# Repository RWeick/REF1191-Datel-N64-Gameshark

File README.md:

# REF1191-Datel-N64-Gameshark
The Kicad files for the REF1191 N64 Gameshark PCB

The edge connector spacing has been corrected from Datel's 2.54 mm to the N64 spec of 2.5 mm.

PCB Thickness: 1.2 mm

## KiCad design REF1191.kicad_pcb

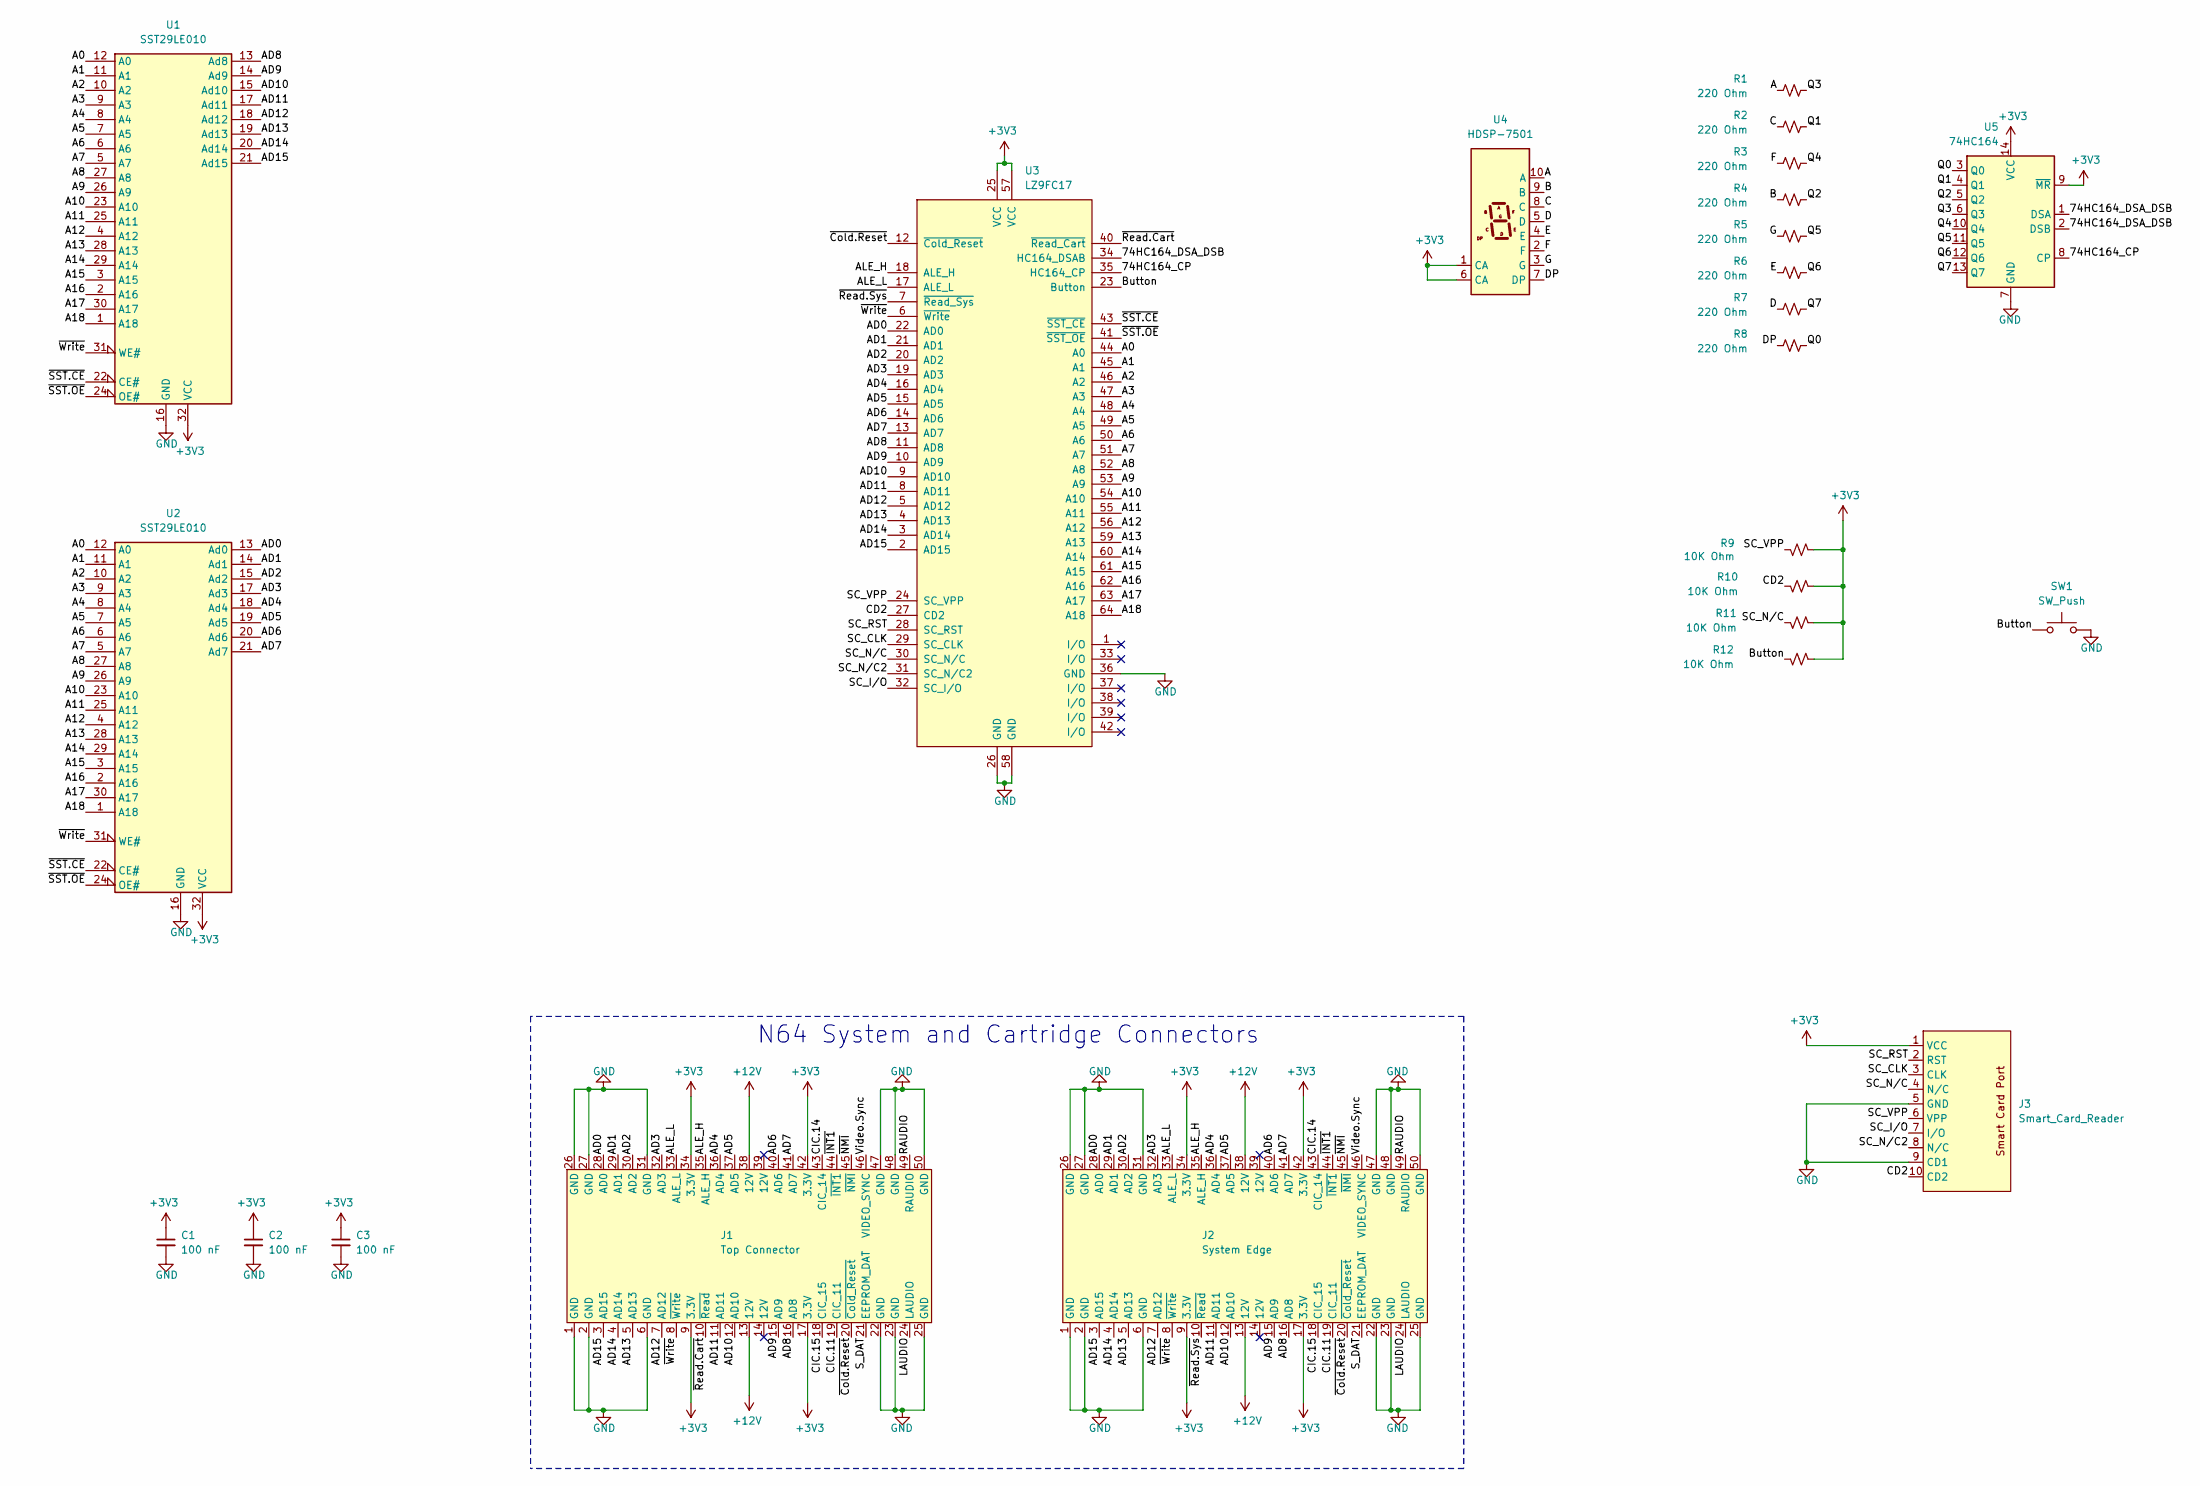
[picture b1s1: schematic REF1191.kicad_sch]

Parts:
C1, C2, C3: 100 nF; 1206 Cap Res
J1: Top Connector; Edge Connector
J2: System Edge; Edge Connector
J3: Smart_Card_Reader; Smart Card Port
R1, R2, R3, R4, R5, R6, R7, R8: 220 Ohm; 0805 Res
R9, R10, R11, R12: 10K Ohm; 1206 Cap Res
SW1: SW_Push; Button
U1, U2: SST29LE010; EEPROM
U3: LZ9FC17
U4: HDSP-7501
U5: 74HC164

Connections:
+3V3: C1.1, C2.1, C3.1, J1.9 (3.3V), J1.17 (3.3V), J1.34 (3.3V), J1.42 (3.3V), J2.9 (3.3V), J2.17 (3.3V), J2.34 (3.3V), J2.42 (3.3V), J3.1 (VCC), R9.2, R10.2, R11.2, R12.2, U1.32 (VCC), U2.32 (VCC), U3.25 (VCC), U3.57 (VCC), U4.1 (CA), U4.6 (CA), U5.9 (~MR), U5.14 (VCC)
+12V: J1.13 (12V), J1.38 (12V), J2.13 (12V), J2.38 (12V)
/74HC164_CP: U3.35 (HC164_CP), U5.8 (CP)
/74HC164_DSA_DSB: U3.34 (HC164_DSAB), U5.1 (DSA), U5.2 (DSB)
/A: R1.1, U4.10 (A)
/A0: U1.12 (A0), U2.12 (A0), U3.44 (A0)
/A1: U1.11 (A1), U2.11 (A1), U3.45 (A1)
/A2: U1.10 (A2), U2.10 (A2), U3.46 (A2)
/A3: U1.9 (A3), U2.9 (A3), U3.47 (A3)
/A4: U1.8 (A4), U2.8 (A4), U3.48 (A4)
/A5: U1.7 (A5), U2.7 (A5), U3.49 (A5)
/A6: U1.6 (A6), U2.6 (A6), U3.50 (A6)
/A7: U1.5 (A7), U2.5 (A7), U3.51 (A7)
/A8: U1.27 (A8), U2.27 (A8), U3.52 (A8)
/A9: U1.26 (A9), U2.26 (A9), U3.53 (A9)
/A10: U1.23 (A10), U2.23 (A10), U3.54 (A10)
/A11: U1.25 (A11), U2.25 (A11), U3.55 (A11)
/A12: U1.4 (A12), U2.4 (A12), U3.56 (A12)
/A13: U1.28 (A13), U2.28 (A13), U3.59 (A13)
/A14: U1.29 (A14), U2.29 (A14), U3.60 (A14)
/A15: U1.3 (A15), U2.3 (A15), U3.61 (A15)
/A16: U1.2 (A16), U2.2 (A16), U3.62 (A16)
/A17: U1.30 (A17), U2.30 (A17), U3.63 (A17)
/A18: U1.1 (A18), U2.1 (A18), U3.64 (A18)
/AD0: J1.28 (AD0), J2.28 (AD0), U2.13 (Ad0), U3.22 (AD0)
/AD1: J1.29 (AD1), J2.29 (AD1), U2.14 (Ad1), U3.21 (AD1)
/AD2: J1.30 (AD2), J2.30 (AD2), U2.15 (Ad2), U3.20 (AD2)
/AD3: J1.32 (AD3), J2.32 (AD3), U2.17 (Ad3), U3.19 (AD3)
/AD4: J1.36 (AD4), J2.36 (AD4), U2.18 (Ad4), U3.16 (AD4)
/AD5: J1.37 (AD5), J2.37 (AD5), U2.19 (Ad5), U3.15 (AD5)
/AD6: J1.40 (AD6), J2.40 (AD6), U2.20 (Ad6), U3.14 (AD6)
/AD7: J1.41 (AD7), J2.41 (AD7), U2.21 (Ad7), U3.13 (AD7)
/AD8: J1.16 (AD8), J2.16 (AD8), U1.13 (Ad8), U3.11 (AD8)
/AD9: J1.15 (AD9), J2.15 (AD9), U1.14 (Ad9), U3.10 (AD9)
/AD10: J1.12 (AD10), J2.12 (AD10), U1.15 (Ad10), U3.9 (AD10)
/AD11: J1.11 (AD11), J2.11 (AD11), U1.17 (Ad11), U3.8 (AD11)
/AD12: J1.7 (AD12), J2.7 (AD12), U1.18 (Ad12), U3.5 (AD12)
/AD13: J1.5 (AD13), J2.5 (AD13), U1.19 (Ad13), U3.4 (AD13)
/AD14: J1.4 (AD14), J2.4 (AD14), U1.20 (Ad14), U3.3 (AD14)
/AD15: J1.3 (AD15), J2.3 (AD15), U1.21 (Ad15), U3.2 (AD15)
/ALE_H: J1.35 (ALE_H), J2.35 (ALE_H), U3.18 (ALE_H)
/ALE_L: J1.33 (ALE_L), J2.33 (ALE_L), U3.17 (ALE_L)
/B: R4.1, U4.9 (B)
/Button: R12.1, SW1.1, U3.23 (Button)
/C: R2.1, U4.8 (C)
/CD2: J3.10 (CD2), R10.1, U3.27 (CD2)
/CIC.11: J1.19 (CIC_11), J2.19 (CIC_11)
/CIC.14: J1.43 (CIC_14), J2.43 (CIC_14)
/CIC.15: J1.18 (CIC_15), J2.18 (CIC_15)
/D: R7.1, U4.5 (D)
/DP: R8.1, U4.7 (DP)
/E: R6.1, U4.4 (E)
/F: R3.1, U4.2 (F)
/G: R5.1, U4.3 (G)
/LAUDIO: J1.24 (LAUDIO), J2.24 (LAUDIO)
/Q0: R8.2, U5.3 (Q0)
/Q1: R2.2, U5.4 (Q1)
/Q2: R4.2, U5.5 (Q2)
/Q3: R1.2, U5.6 (Q3)
/Q4: R3.2, U5.10 (Q4)
/Q5: R5.2, U5.11 (Q5)
/Q6: R6.2, U5.12 (Q6)
/Q7: R7.2, U5.13 (Q7)
/RAUDIO: J1.49 (RAUDIO), J2.49 (RAUDIO)
/SC_CLK: J3.3 (CLK), U3.29 (SC_CLK)
/SC_I/O: J3.7 (I/O), U3.32 (SC_I/O)
/SC_N/C: J3.4 (N/C), R11.1, U3.30 (SC_N/C)
/SC_N/C2: J3.8 (N/C), U3.31 (SC_N/C2)
/SC_RST: J3.2 (RST), U3.28 (SC_RST)
/SC_VPP: J3.6 (VPP), R9.1, U3.24 (SC_VPP)
/S_DAT: J1.21 (EEPROM_DAT), J2.21 (EEPROM_DAT)
/Video.Sync: J1.46 (VIDEO_SYNC), J2.46 (VIDEO_SYNC)
/~Cold.Reset: J1.20 (~Cold_Reset), J2.20 (~Cold_Reset), U3.12 (~Cold_Reset)
/~INT1: J1.44 (~INT1), J2.44 (~INT1)
/~NMI: J1.45 (~NMI), J2.45 (~NMI)
/~Read.Cart: J1.10 (~Read), U3.40 (~Read_Cart)
/~Read.Sys: J2.10 (~Read), U3.7 (~Read_Sys)
/~SST.CE: U1.22 (CE#), U2.22 (CE#), U3.43 (~SST_CE)
/~SST.OE: U1.24 (OE#), U2.24 (OE#), U3.41 (~SST_OE)
/~Write: J1.8 (~Write), J2.8 (~Write), U1.31 (WE#), U2.31 (WE#), U3.6 (~Write)
GND: C1.2, C2.2, C3.2, J1.1 (GND), J1.2 (GND), J1.6 (GND), J1.22 (GND), J1.23 (GND), J1.25 (GND), J1.26 (GND), J1.27 (GND), J1.31 (GND), J1.47 (GND), J1.48 (GND), J1.50 (GND), J2.1 (GND), J2.2 (GND), J2.6 (GND), J2.22 (GND), J2.23 (GND), J2.25 (GND), J2.26 (GND), J2.27 (GND), J2.31 (GND), J2.47 (GND), J2.48 (GND), J2.50 (GND), J3.5 (GND), J3.9 (CD1), SW1.2, U1.16 (GND), U2.16 (GND), U3.26 (GND), U3.36 (GND), U3.58 (GND), U5.7 (GND)

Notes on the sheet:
N64 System and Cartridge Connectors

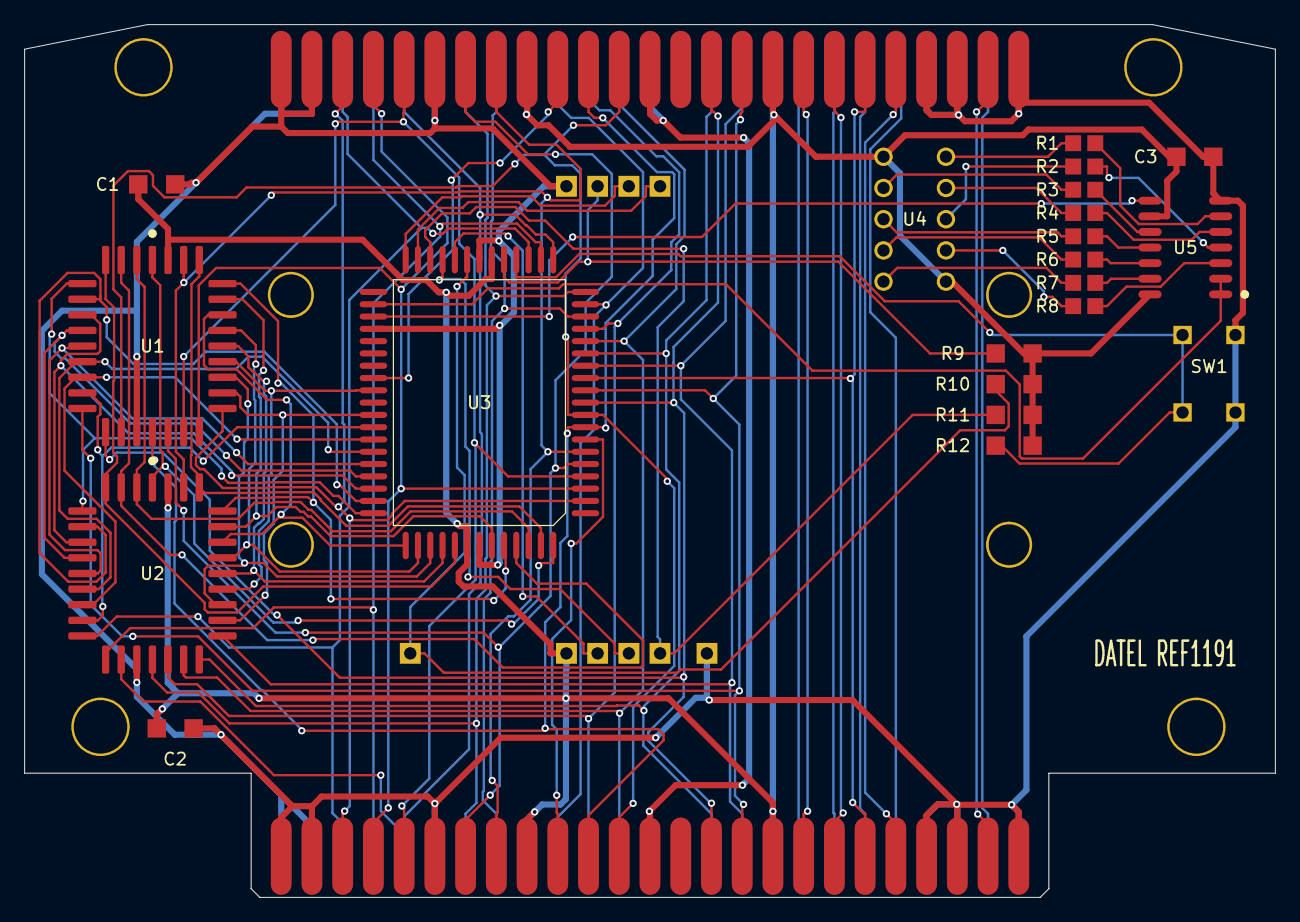
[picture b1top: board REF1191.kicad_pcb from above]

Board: 2 copper layers, 101.8 x 71.0 mm, 25 parts (0 on the bottom side), 81 nets.

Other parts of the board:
Holes: Drill Holes
